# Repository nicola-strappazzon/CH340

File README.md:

# CH340

Este es un simple CI que permite la comunicación USB 2.0 a Serial & UPDI de muy bajo coste, diseñado y fabricado en china por [Jiangsu Heng Qin Ltd. (WCH)](http://www.wch-ic.com). Para usar el CI conectado a un ordenador/computadora, necesitas tener instalado el driver. De momento nos vamos a centrar en el CH340C/B que tiene unas prestaciones muy versátiles, entre ellas destacan las siguientes:

- Las versiones CH340C/N/K/E/X/B tiene reloj integrado, no requiere cristal externo. CH340B también integra una EEPROM utilizada para configurar el número de serie, etc.
- USB 2.0 a Serial, compatible con RS232, RS485, RS422.
- Usa el protocolo UART para comunicarse con el MCU.
- Soporta 5v y 3.3v.

También podemos configurar el UART para Unified Program and Debug Interface (UPDI) que es habitual para programar los Microcontroladores (MCU) como el AVR Dx.

En la imagen mostramos el circuito básico y la conexión con un ATMega328P.

Puedes conseguir los IC en la tienda oficial del fabricante en [AliExpress](https://wchofficialstore.es.aliexpress.com/store/1100367542) o en un distribuidor autorizado en china [LCSC](https://www.lcsc.com).

## Esquema mínimo

Con este CI podemos comunicarnos a un MCU usando el protocolo Serial o para algunos programarlos mediante UPDI.

### Serial

#### Componentes

Use los siguientes componentes para construir el circuito mínimo:

- Un IC CH340C.
- Condensador de 0.1uF (Código: 104, Cantidad: 2).
- Condensador de 10nF.
- Condensador de 100nF.

### UPDI

#### Componentes

- Un IC CH340C.
- Condensador de 0.1uF (Código: 104, Cantidad: 2).
- Condensador de 10nF.
- Condensador de 100nF.
- Resistencia de 470 ohm.
- Diodo schottky 1N5817 (puede ser otro).

## Driver

Dependiendo del sistema operativo (OS) que use, deberá instalar uno de los siguientes controladores.

- [Linux](https://www.wch-ic.com/downloads/CH341SER_LINUX_ZIP.html)
- [MacOS](https://www.wch-ic.com/downloads/CH341SER_MAC_ZIP.html)
- [Windows](https://www.wch-ic.com/downloads/CH341SER_ZIP.html)

## Proyectos relacionados

- [CH334 - HUB USB 2.0](https://github.com/nicola-strappazzon/CH334)
- [CH552 - 8-bits MCU - 8051](https://github.com/nicola-strappazzon/CH552)
- [CH9141 - Bluetooth Serial Transparent](https://github.com/nicola-strappazzon/CH9141)

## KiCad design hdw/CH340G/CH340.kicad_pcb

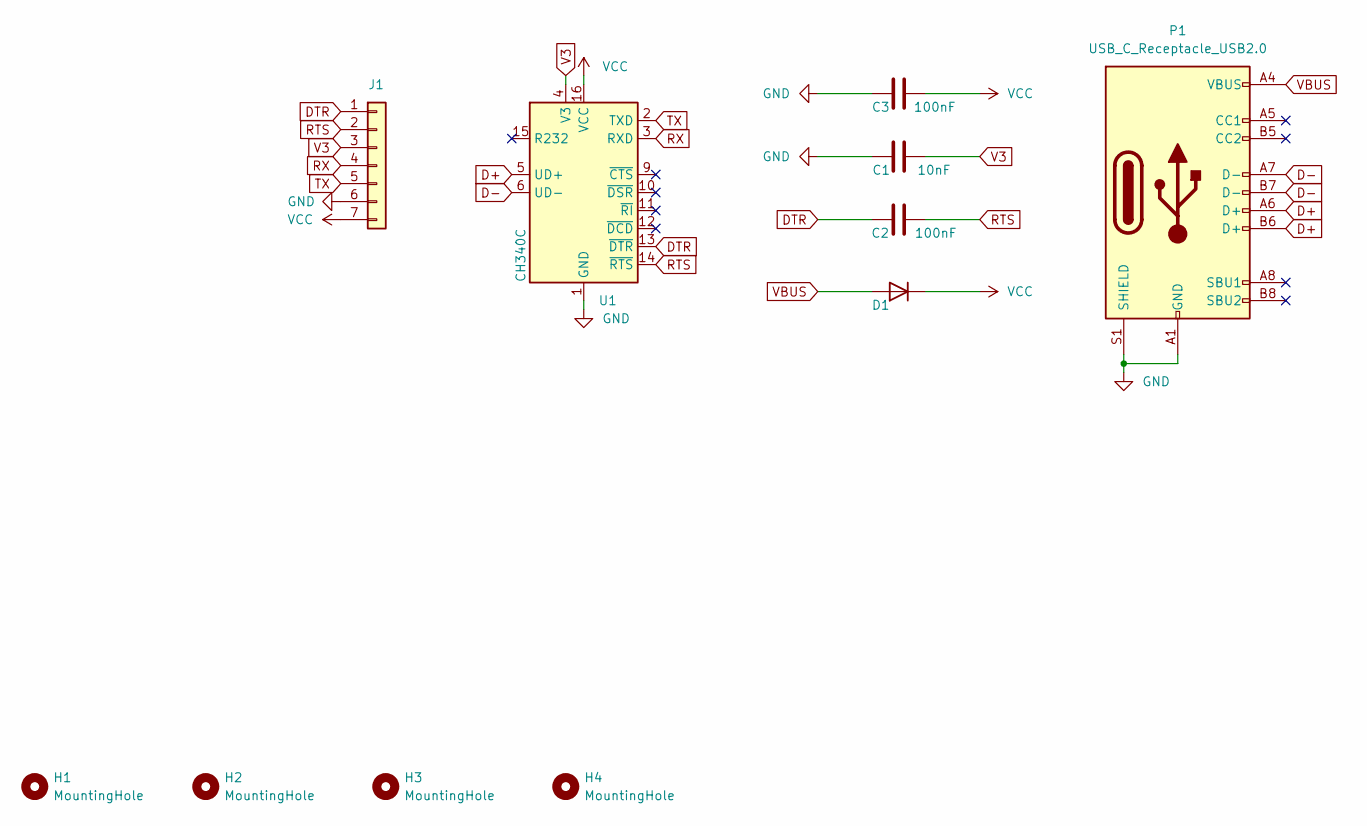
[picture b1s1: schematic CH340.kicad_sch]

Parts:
C1: 10nF; C1206
C2, C3: 100nF; C1206
D1: D; SMA_DO_214AC
H1, H2, H3, H4: MountingHole; MountingHole_3.2mm_M3
J1: Conn_01x07; PinHeader_1x07_P2.54mm
P1: USB_C_Receptacle_USB2.0; TH_USB_C
U1: CH340C; SOIC-16_3.9x9.9mm_P1.27mm

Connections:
D+: P1.A6 (D+), P1.B6 (D+), U1.5 (UD+)
D-: P1.A7 (D-), P1.B7 (D-), U1.6 (UD-)
DTR: C2.1, J1.1, U1.13 (~DTR)
GND: C1.2, C3.2, J1.6, P1.A1 (GND), P1.A12 (GND), P1.B1 (GND), P1.B12 (GND), P1.S1 (SHIELD), U1.1 (GND)
RTS: C2.2, J1.2, U1.14 (~RTS)
RX: J1.4, U1.3 (RXD)
TX: J1.5, U1.2 (TXD)
V3: C1.1, J1.3, U1.4 (V3)
VBUS: D1.2 (A), P1.A4 (VBUS), P1.A9 (VBUS), P1.B4 (VBUS), P1.B9 (VBUS)
VCC: C3.1, D1.1 (K), J1.7, U1.16 (VCC)

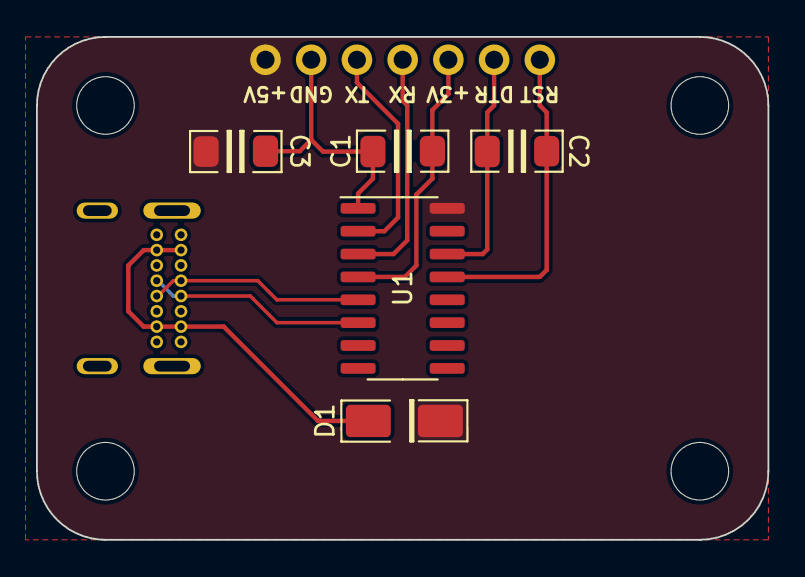
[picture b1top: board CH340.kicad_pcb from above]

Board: 2 copper layers, 40.6 x 27.9 mm, 11 parts (0 on the bottom side), 10 nets.

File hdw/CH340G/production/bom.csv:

Designator,Footprint,Quantity,Value,LCSC Part #
C1,C1206,1,10nF,
"C2, C3",C1206,2,100nF,
D1,SMA_DO_214AC,1,D,
"H1, H2, H3, H4",MountingHole_3.2mm_M3,4,MountingHole,
J1,PinHeader_1x07_P2.54mm,1,Conn_01x07,
P1,TH_USB_C,1,USB_C_Receptacle_USB2.0,
U1,SOIC-16_3.9x9.9mm_P1.27mm,1,CH340C,

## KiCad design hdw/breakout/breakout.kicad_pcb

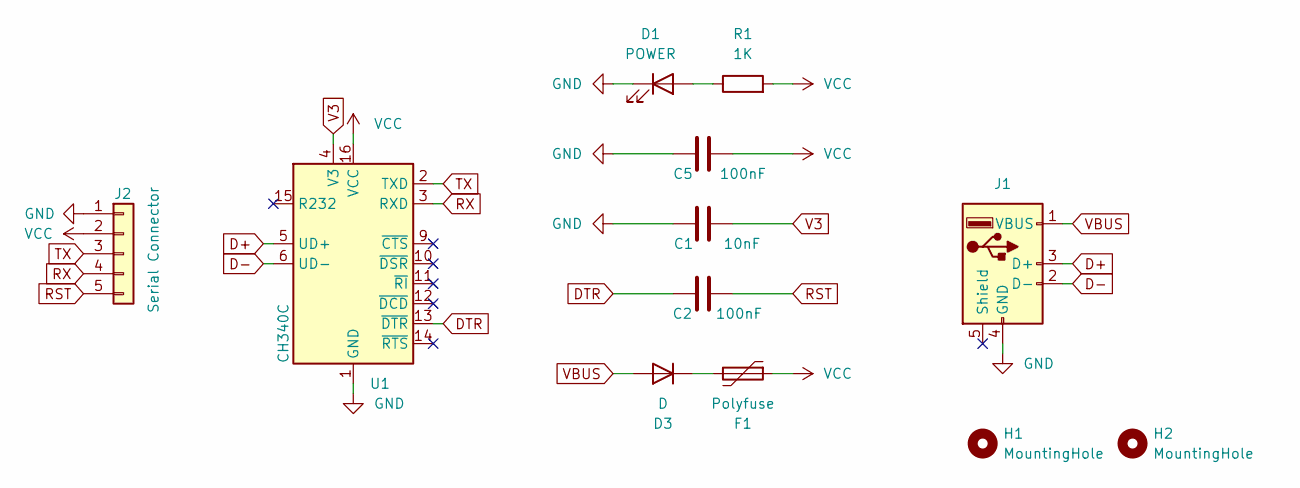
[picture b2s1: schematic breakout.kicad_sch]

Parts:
C1: 10nF; C1206
C2, C5: 100nF; C1206
D1: POWER; L1206
D3: D; D1206
F1: Polyfuse; F1206
H1, H2: MountingHole; MountingHole_2.2mm_M2_DIN965
J1: USB_A; USB_Micro-B
J2: Serial Connector; PinHeader_1x05_P2.54mm_Vertical
R1: 1K; R1206
U1: CH340C; SOIC-16_3.9x9.9mm_P1.27mm

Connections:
D+: J1.3 (D+), U1.5 (UD+)
D-: J1.2 (D-), U1.6 (UD-)
DTR: C2.1, U1.13 (~DTR)
GND: C1.2, C5.2, D1.1 (K), J1.4 (GND), J2.1, U1.1 (GND)
unnamed: D1.2 (A), R1.1
unnamed: D3.1 (K), F1.2
RST: C2.2, J2.5
RX: J2.4, U1.3 (RXD)
TX: J2.3, U1.2 (TXD)
V3: C1.1, U1.4 (V3)
VBUS: D3.2 (A), J1.1 (VBUS)
VCC: C5.1, F1.1, J2.2, R1.2, U1.16 (VCC)

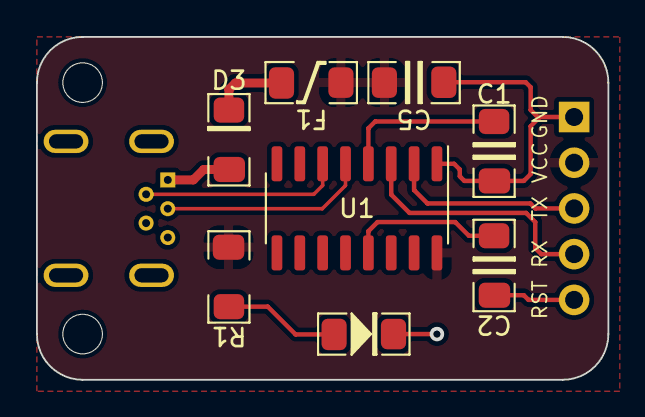
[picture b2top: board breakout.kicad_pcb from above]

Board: 2 copper layers, 31.8 x 19.0 mm, 12 parts (0 on the bottom side), 12 nets.

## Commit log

2024-01-06 doc - update
2024-01-07 doc - update links
2024-01-25 upgrade pcb to use USB C 2.0
2025-05-27 Save changes at: 1748382033
2025-05-27 Save changes at: 1748382114
2025-06-17 Save changes at: 1750157296
2025-07-19 Save changes at: 1752950752
2025-07-19 Save changes at: 1752950858
2025-07-19 Save changes at: 1752950926
2025-07-20 Save changes at: 1753001140
2025-07-20 Save changes at: 1753038091
